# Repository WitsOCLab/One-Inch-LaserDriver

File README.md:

---

# One-Inch-LaserDriver

...

## HowTo

Use this plugin to generate what's required for manufacturing with JLCPCB: https://github.com/Bouni/kicad-jlcpcb-tools

### KiBot

[KiBot](https://github.com/INTI-CMNB/KiBot/) is used to generate all kind of documentation from a KiCAD6 project.

Whenever a file matching `pcb/*.kicad_*` changes this workflow will trigger.

The following documents are generated on every build:

```
- pcb/cad/
   - dxf/
      - AutoCAD - DXF
   - boardview - BRD
   - 3D render - STEP
- pcb/docs/
   - bom/
      - Interactive BOM - HTML
      - Octopart list - CSV
      - KiCost - XLSX (disabled)
   - schematic - PDF
- pcb/img/
   - pcb/$fab/$style/
      - PCB top - SVG
      - PCB bottom - SVG
   - render/ (disabled)
      - PCB render - PNG
   - schematic - SVG
- pcb/gerbers - ZIP
```

### REUSE

Used to ensure every file got a propper license. 

## getting started

- [ ] PCB
   - [ ] change the filenames in `pcb/*.kicad_*` matching your repository name
   - [ ] create your PCB
- [ ] run `reuse --lint`
   - [ ] make sure the licenses of `pcb/*` fits your needs
- [ ] commit and push all those changes regulary to your project

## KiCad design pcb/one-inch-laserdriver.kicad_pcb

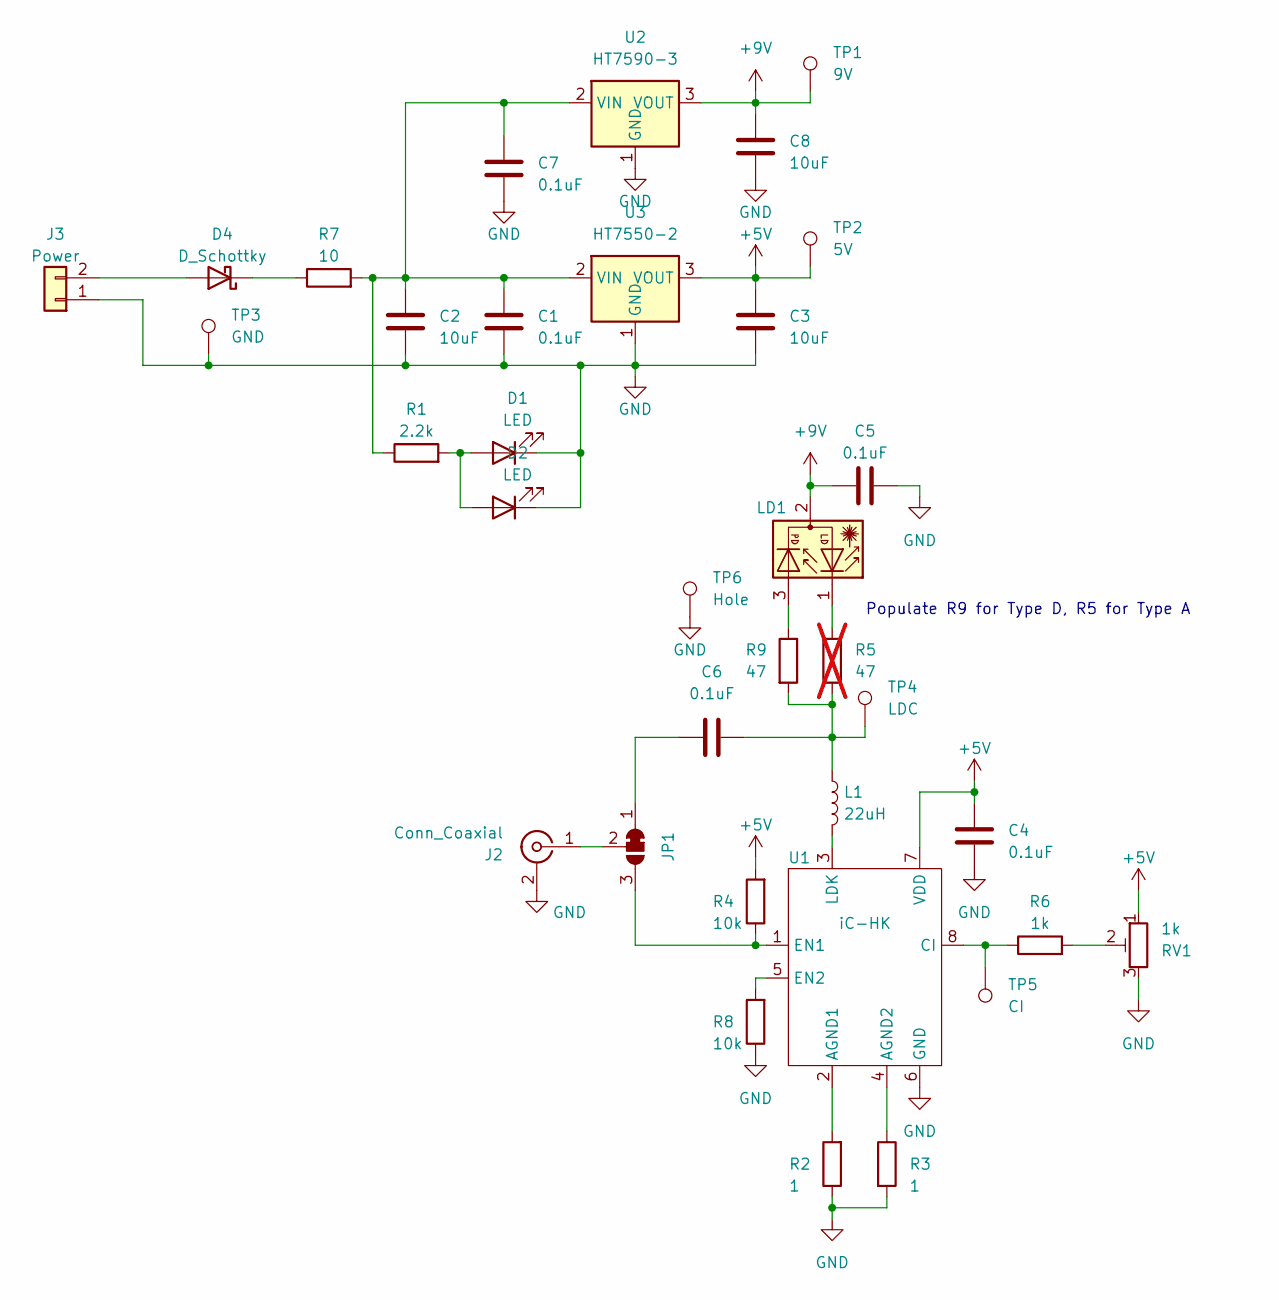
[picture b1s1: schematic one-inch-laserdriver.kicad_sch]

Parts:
C1, C4, C5, C6, C7: 0.1uF; C_0402_1005Metric; LCSC C307331
C2, C3, C8: 10uF; C_0603_1608Metric; LCSC C96446
D1, D2: LED; LED_0603_1608Metric; LCSC C72043
D4: D_Schottky; D_SOD-123; LCSC C8598
J2: Conn_Coaxial; MMCX_Molex_73415-1471_Vertical; LCSC C5137198
J3: Power; PinHeader_1x02_P2.54mm_Vertical
JP1: SolderJumper_3_Bridged12; SolderJumper-3_P1.3mm_Open_RoundedPad1.0x1.5mm_NumberLabels
L1: 22uH; L_Sunlord_SWPA4018S; LCSC C83443
LD1: D_Laser_Photo_NType; LaserDiode_TO18-D5.6-3
R1: 2.2k; R_0603_1608Metric; LCSC C4190
R2, R3: 1; R_0603_1608Metric; LCSC C22936
R4, R8: 10k; R_0603_1608Metric; LCSC C25804
R5: 47; R_0402_1005Metric; LCSC C25118; not fitted
R6: 1k; R_0603_1608Metric; LCSC C21190
R7: 10; R_0603_1608Metric; LCSC C22859
R9: 47; R_0402_1005Metric; LCSC C25118
RV1: 1k; Potentiometer_Bourns_3314G_Vertical; LCSC C780221
TP1: 9V; TestPoint_THTPad_D1.0mm_Drill0.5mm
TP2: 5V; TestPoint_THTPad_D1.0mm_Drill0.5mm
TP3: GND; TestPoint_THTPad_D1.0mm_Drill0.5mm
TP4: LDC; TestPoint_THTPad_D1.0mm_Drill0.5mm
TP5: CI; TestPoint_THTPad_D1.0mm_Drill0.5mm
TP6: Hole; TestPoint_THTPad_D1.0mm_Drill0.5mm
U1: iC-HK; SO-8_3.9x4.9mm_P1.27mm
U2: HT7590-3; SOT-23-5; LCSC C259667
U3: HT7550-2; SOT-23-5; LCSC C81799

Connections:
+5V: C3.1, C4.1, R4.2, RV1.1, TP2.1, U1.7 (VDD), U3.3 (VOUT)
+9V: C5.1, C8.1, LD1.2, TP1.1, U2.3 (VOUT)
GND: C1.2, C2.2, C3.2, C4.2, C5.2, C7.2, C8.2, D1.1 (K), D2.1 (K), J2.2 (Ext), J3.1, R2.1, R3.2, R8.1, RV1.3, TP3.1, TP6.1, U1.6 (GND), U2.1 (GND), U3.1 (GND)
unnamed: C6.2, L1.1, R5.1, R9.2, TP4.1
unnamed: D1.2 (A), D2.2 (A), R1.2
unnamed: D4.2 (A), J3.2
unnamed: D4.1 (K), R7.1
unnamed: J2.1 (In), JP1.2 (C)
unnamed: C6.1, JP1.1 (A)
unnamed: JP1.3 (B), R4.1, U1.1 (EN1)
unnamed: LD1.1, R5.2
unnamed: LD1.3, R9.1
unnamed: R6.2, RV1.2
unnamed: R2.2, U1.2 (AGND1)
unnamed: R3.1, U1.4 (AGND2)
unnamed: R6.1, TP5.1, U1.8 (CI)
unnamed: R8.2, U1.5 (EN2)
unnamed: L1.2, U1.3 (LDK)
unnamed: C1.1, C2.1, C7.1, R1.1, R7.2, U2.2 (VIN), U3.2 (VIN)

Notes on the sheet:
Populate R9 for Type D, R5 for Type A

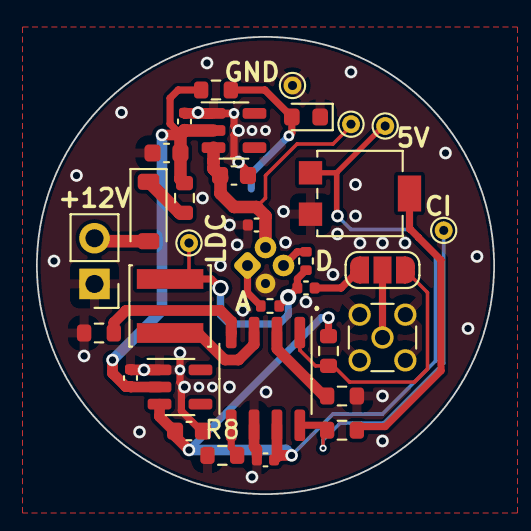
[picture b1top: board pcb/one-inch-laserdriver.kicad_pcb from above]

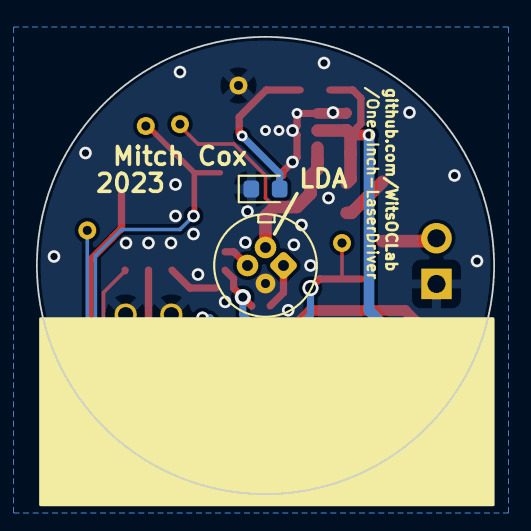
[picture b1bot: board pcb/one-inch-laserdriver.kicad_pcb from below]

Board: 2 copper layers, 25.4 x 25.4 mm, 35 parts (2 on the bottom side), 19 nets.

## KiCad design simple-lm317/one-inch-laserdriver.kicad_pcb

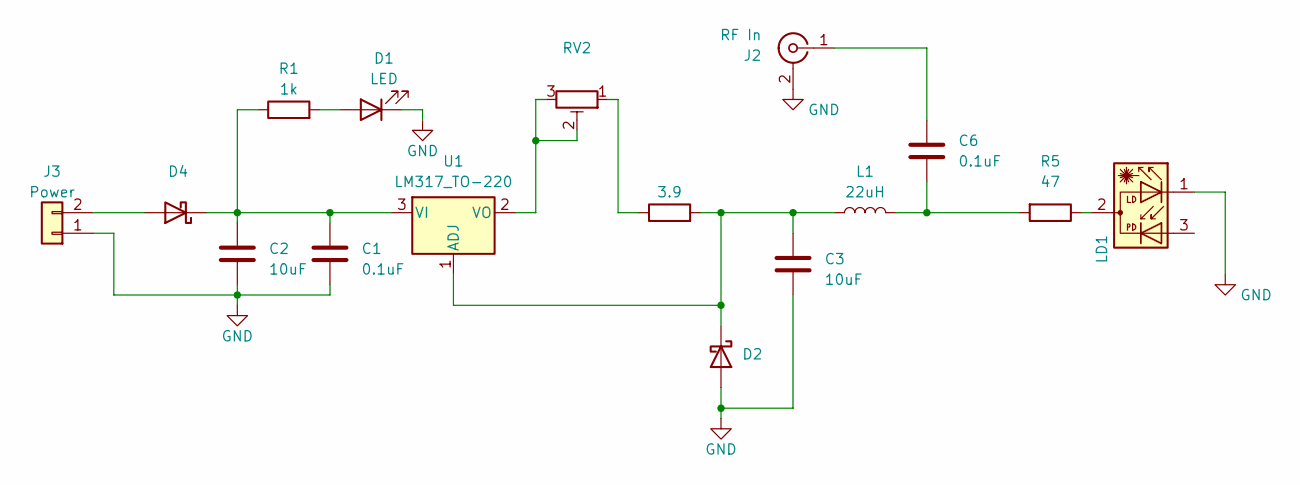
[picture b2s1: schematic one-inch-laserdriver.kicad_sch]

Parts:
C1, C6: 0.1uF; C_0603_1608Metric
C2, C3: 10uF; C_0603_1608Metric
D1: LED; LED_0603_1608Metric
D2, D4: D_SOD-123; LCSC C8598
J2: RF In; MMCX_Molex_73415-1471_Vertical
J3: Power; PinHeader_1x02_P2.54mm_Vertical
L1: 22uH; R_0603_1608Metric
LD1: D_Laser_Photo_NType; LaserDiode_TO18-D5.6-3
R1: 1k; R_0603_1608Metric
R5: 47; R_0603_1608Metric
R6: 3.9; R_0603_1608Metric
RV2: 200; Potentiometer_Bourns_3296W_Vertical; LCSC C780221
U1: LM317_TO-220; TO-220-3_Vertical

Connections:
GND: C1.2, C2.2, C3.2, D1.1 (K), D2.2 (A), J2.2 (Ext), J3.1, LD1.1
unnamed: C6.1, L1.2, R5.2
unnamed: D1.2 (A), R1.2
unnamed: C3.1, D2.1 (K), L1.1, R6.2, U1.1 (ADJ)
unnamed: D4.2 (A), J3.2
unnamed: C1.1, C2.1, D4.1 (K), R1.1, U1.3 (VI)
unnamed: C6.2, J2.1 (In)
unnamed: LD1.2, R5.1
unnamed 8: R6.1, RV2.1; also elsewhere on the board
unnamed 9: RV2.2, RV2.3, U1.2 (VO); also elsewhere on the board

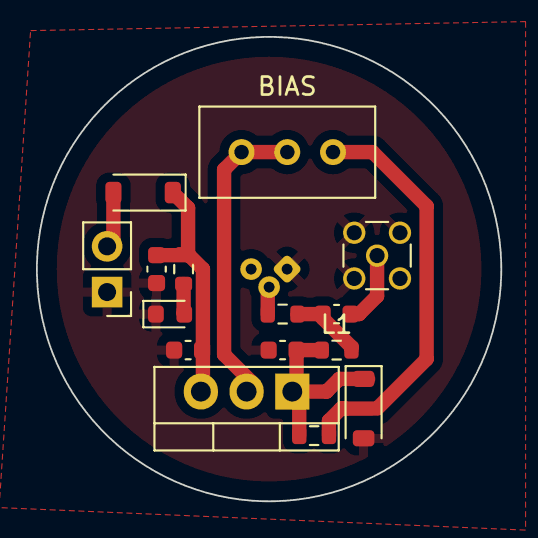
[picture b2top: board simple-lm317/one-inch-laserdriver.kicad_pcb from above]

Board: 2 copper layers, 25.8 x 25.8 mm, 16 parts (1 on the bottom side), 10 nets.

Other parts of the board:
BIAS: 200; Potentiometer_Bourns_3296W_Vertical

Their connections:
unnamed 8: BIAS.1; also elsewhere on the board
unnamed 9: BIAS.2, BIAS.3; also elsewhere on the board

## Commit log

2023-07-27 templates
2023-07-27 remove src
2023-07-27 Update kibot.yml to ki7
2023-07-27 almost done v1
2023-07-31 bias tee
2023-09-10 ic-HKb version done
2024-11-02 working. standard design
